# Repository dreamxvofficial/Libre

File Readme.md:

# Libre By DreamXV #
## It is an E-Ink Reading Device made for portability and mostly for warm-up week of *halflife.hackclub.com*. I have always been a fan of Kindle but its price is too high and it is not that customizable so I thought of making my own e-ink reader. ##
---
## Specs ##
- **Processor** ESP32-S3-WROOM-1-N16R8
- **Display** Waveshare 4.2", 400×300, B/W, SPI
- **Battery** 3.7 V Li-Po, 2000 mAh
- **MicroSD card**	16/32 GB 
- **USB-C** USB 2.0 Type-C receptacle
- **5 UI buttons** 6×6 × ~5 mm tactile push button
- **Power switch** SPDT slide switch

## Inspo Look ##

## Approximate BOM : ##

| Part            | Specification                   | Qty |
| --------------- | ------------------------------- | --: |
| E-Ink Display   | Waveshare 4.2" 400×300 B/W, SPI |   1 |
| Microcontroller | ESP32-S3-DevKitC-1-N16R8V       |   1 |
| Storage         | 16–32GB MicroSD Card + Socket   |   1 |
| Battery         | 3.7V 3000mAh Li-Po              |   1 |
| Charging        | MCP73831 Li-Po Charging Circuit |   1 |
| Power Switch    | SPDT ON/OFF Slide Switch        |   1 |
| Navigation      | 6×6mm SMD Tactile Buttons       |   5 |
| PCB             | Custom 2-Layer PCB              |   1 |
| Enclosure       | Custom 3D-Printed Case          |   1 |

## ** Approximate BOM ~ $110 or ~₹10,500 INR ** ##

## Schematic ##
### So i used AI for planing the connections of schematics and it just made me wanna die so yeah i dont know what to write more but i have connected the screen mcu micro sd and buttons together i dont know how but yes i have connected ###

## PCB ## 
### I just wanna give up mannnnnnnnnnn! >>>>>>>>>>3 I had to change the whole design as PCB was not as size of CAD so here is the new PCB with MCU ESP 32, 5 buttons 1 slider button and Micro SD Card ##

## CAD ##
### CAD design for Libre. It is 130 mm height and 78.5 mm width with a space for PCB, Buttons and E-Ink Display ##

## Final BOM ##

# DreamXV Libre — Final BOM

| Part | Qty | Unit Price (INR) | Total (INR) | Price Basis | Design Ref |
|---|---:|---:|---:|---|---|
| Waveshare 4.2-inch E-Ink Module B, 400x300 | 1 | ₹4,861.00 | ₹4,861.00 | Amazon India / current listing checked | Main display |
| ESP32-S3-DEVKITC-1-N16R8V | 1 | ₹1,500.00 | ₹1,500.00 | Indian/Amazon market listing checked | Main MCU board |
| Li-Po battery 3.7V 3000mAh | 1 | ₹500.00 | ₹500.00 | Indian hobby-retailer budget | Battery |
| Custom PCB | 1 | ₹1,000.00 | ₹1,000.00 | User budget | PCB fabrication |
| 3D-printed enclosure | 1 | ₹960.00 | ₹960.00 | User budget: $10 | 3D printing |
| Molex 104031-0811 MicroSD socket | 1 | ₹100.00 | ₹100.00 | Indian distributor budget | J2 |
| JST-PH 2-pin battery connector | 1 | ₹40.00 | ₹40.00 | Indian hobby-retailer budget | J3 |
| 8-pin display connector/header | 1 | ₹50.00 | ₹50.00 | Indian hobby-retailer budget | J1 |
| MCP73831-2-OT Li-Po charger IC | 1 | ₹80.00 | ₹80.00 | Indian distributor budget | U2 |
| AP2112K-3.3 LDO | 1 | ₹50.00 | ₹50.00 | Indian distributor budget | U3 |
| TL3305AF160QG SMD tactile button | 5 | ₹48.00 | ₹240.00 | Robu India listing | SW1-SW5 |
| C&K JS102011SAQN SPDT SMD switch | 1 | ₹150.00 | ₹150.00 | Indian distributor budget | SW6 |
| 1uF 0805 MLCC | 2 | ₹10.00 | ₹20.00 | Robu India example | C1-C2 |
| 4.7uF MLCC | 2 | ₹15.00 | ₹30.00 | Indian distributor budget | C3-C4 |
| 100nF 0805 MLCC | 1 | ₹3.00 | ₹3.00 | Indian distributor budget | C5 |
| 2kΩ 0805 resistor | 1 | ₹2.00 | ₹2.00 | Indian distributor budget | R1 |
| 200kΩ 0805 resistor | 2 | ₹0.31 | ₹0.62 | Robu India example | R2-R3 |

## Total Cost

- **Total INR:** ₹9,586.62
- **Exchange Rate:** ₹95.95 = $1
- **Total USD:** $99.91
- **Budget:** $100
- **Status:** UNDER $100

## Firmware ##

### ** The firmware is written for the ESP32-S3 and handles the main functions of Libre like the E-Ink display, MicroSD card, 5 navigation buttons and battery monitoring. It also has a simple file browser for selecting books and basic TXT reading. PDF files can be detected and listed, with proper PDF rendering planned for a future version. ** ###

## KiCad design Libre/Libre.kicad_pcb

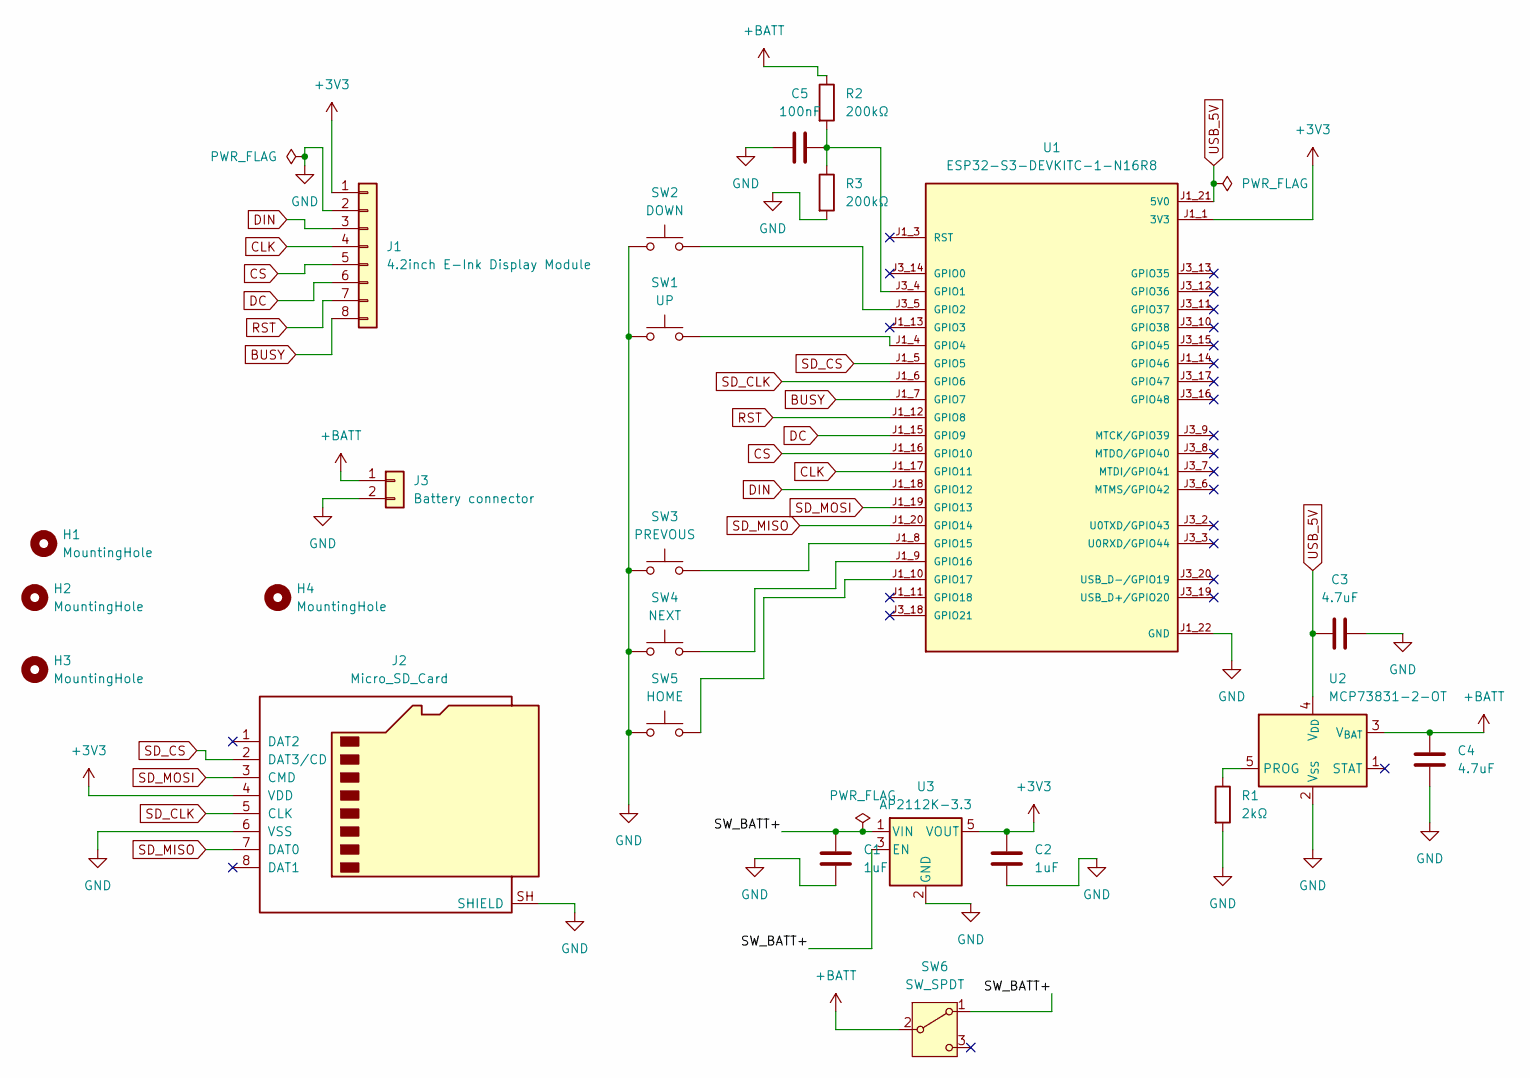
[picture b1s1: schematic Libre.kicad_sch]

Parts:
C1, C2: 1uF; C_0603_1608Metric
C3, C4: 4.7uF; C_0805_2012Metric
C5: 100nF; C_0603_1608Metric
H1, H2, H3, H4: MountingHole; MountingHole_2.5mm
J1: 4.2inch E-Ink Display Module; PinHeader_1x08_P2.54mm_Vertical
J2: Micro_SD_Card; microSD_HC_Molex_104031-0811
J3: Battery connector; JST_PH_S2B-PH-K_1x02_P2.00mm_Horizontal
R1: 2kΩ; R_0603_1608Metric
R2, R3: 200kΩ; R_0603_1608Metric
SW1: UP; SW_SPST_TL3305A
SW2: DOWN; SW_SPST_TL3305A
SW3: PREVOUS; SW_SPST_TL3305A
SW4: NEXT; SW_SPST_TL3305A
SW5: HOME; SW_SPST_TL3305A
SW6: SW_SPDT; SW_SPDT_CK_JS102011SAQN
U1: ESP32-S3-DEVKITC-1-N16R8; XCVR_ESP32-S3-DEVKITC-1-N16R8V; PARTREV V1
U2: MCP73831-2-OT; SOT-23-5
U3: AP2112K-3.3; SOT-23-5

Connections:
+3V3: C2.1, J1.1, J2.4 (VDD), U1.J1_1 (3V3), U1.J1_2 (3V3), U3.5 (VOUT)
+BATT: C4.1, J3.1, R2.1, SW6.2 (B), U2.3 (V_{BAT})
/SW_BATT+: C1.1, SW6.1 (A), U3.1 (VIN), U3.3 (EN)
BUSY: J1.8, U1.J1_7 (GPIO7)
CLK: J1.4, U1.J1_17 (GPIO11)
CS: J1.5, U1.J1_16 (GPIO10)
DC: J1.6, U1.J1_15 (GPIO9)
DIN: J1.3, U1.J1_18 (GPIO12)
GND: C1.2, C2.2, C3.2, C4.2, C5.1, J1.2, J2.6 (VSS), J2.SH (SHIELD), J3.2, R1.2, R3.2, SW1.1, SW2.1, SW3.1, SW4.1, SW5.1, U1.J1_22 (GND), U1.J3_1 (GND), U1.J3_21 (GND), U1.J3_22 (GND), U2.2 (V_{SS}), U3.2 (GND)
unnamed: C5.2, R2.2, R3.1, U1.J3_4 (GPIO1)
unnamed: SW2.2, U1.J3_5 (GPIO2)
unnamed: SW1.2, U1.J1_4 (GPIO4)
unnamed: SW3.2, U1.J1_8 (GPIO15)
unnamed: SW4.2, U1.J1_9 (GPIO16)
unnamed: SW5.2, U1.J1_10 (GPIO17)
unnamed: R1.1, U2.5 (PROG)
RST: J1.7, U1.J1_12 (GPIO8)
SD_CLK: J2.5 (CLK), U1.J1_6 (GPIO6)
SD_CS: J2.2 (DAT3/CD), U1.J1_5 (GPIO5)
SD_MISO: J2.7 (DAT0), U1.J1_20 (GPIO14)
SD_MOSI: J2.3 (CMD), U1.J1_19 (GPIO13)
USB_5V: C3.1, U1.J1_21 (5V0), U2.4 (V_{DD})

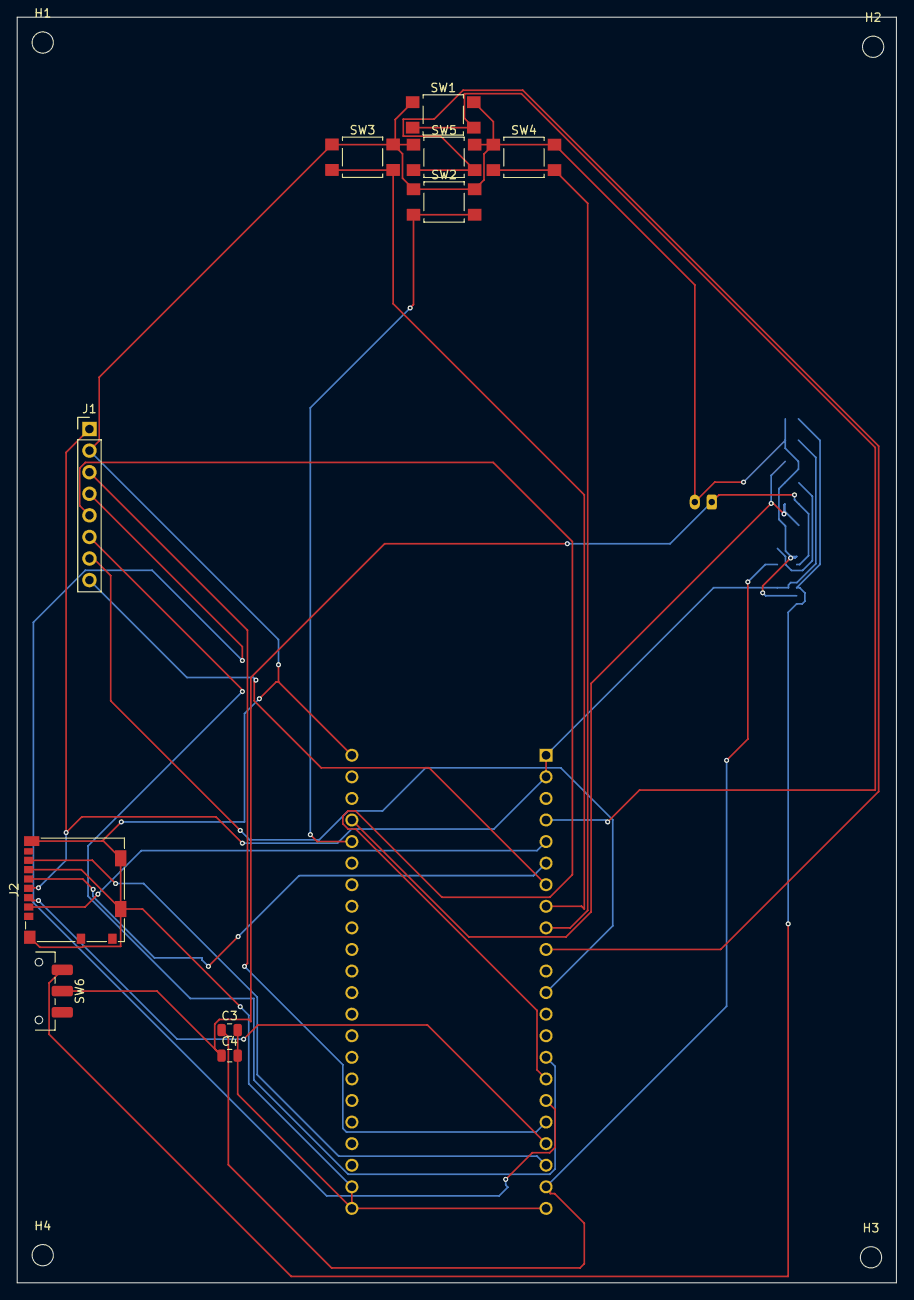
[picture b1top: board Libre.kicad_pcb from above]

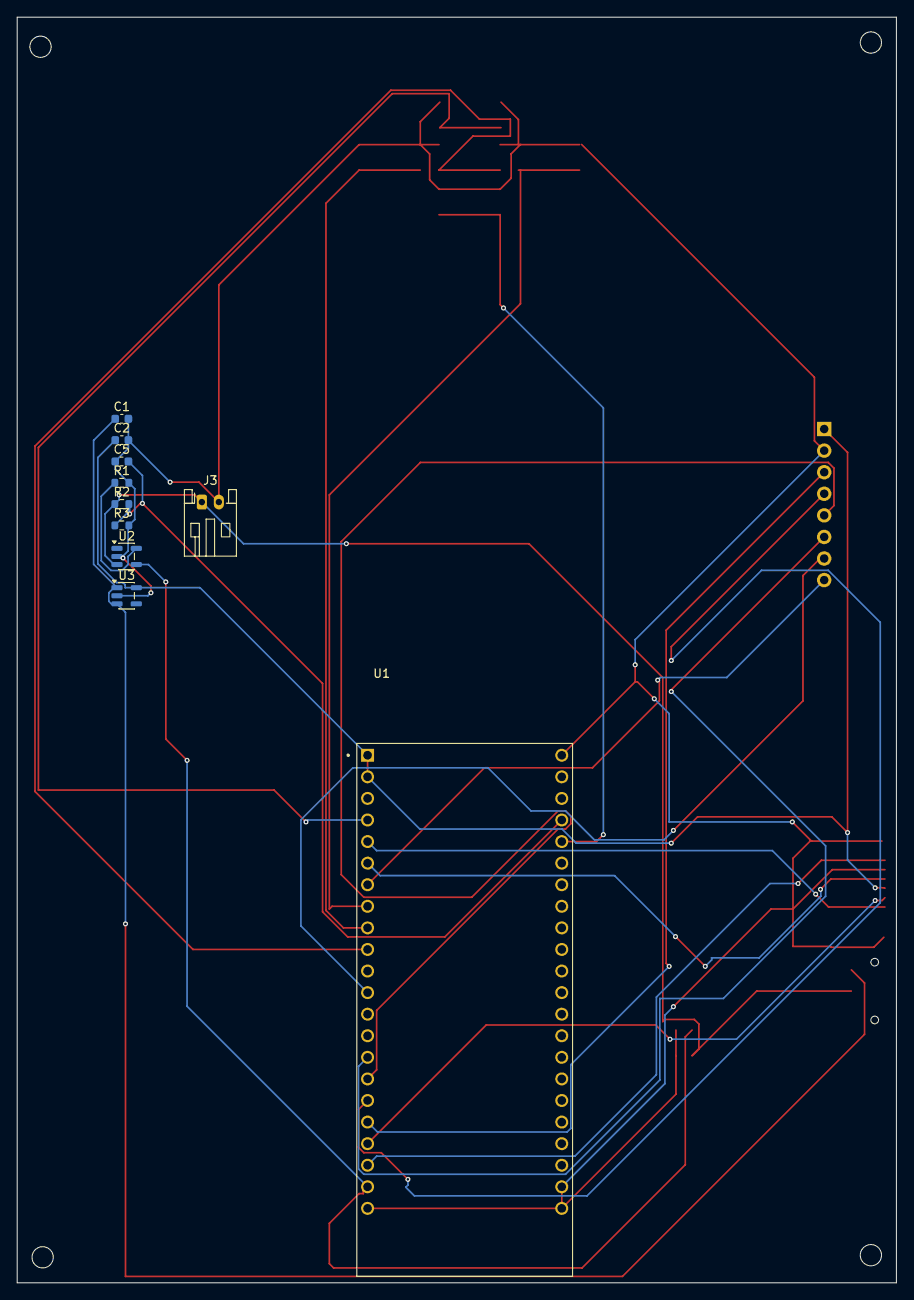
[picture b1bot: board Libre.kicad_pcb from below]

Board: 2 copper layers, 103.5 x 149.0 mm, 24 parts (10 on the bottom side), 22 nets.

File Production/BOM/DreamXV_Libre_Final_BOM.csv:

Part,Qty,Unit Price INR,Total INR,Price Basis,Design Ref
"Waveshare 4.2-inch E-Ink Module B, 400x300",1,4861.0,4861.0,Amazon India / current listing checked,Main display
ESP32-S3-DEVKITC-1-N16R8V,1,1500.0,1500.0,Indian/Amazon market listing checked,Main MCU board
Li-Po battery 3.7V 3000mAh,1,500.0,500.0,Indian hobby-retailer budget,Battery
Custom PCB,1,1000.0,1000.0,User budget,PCB fabrication
3D-printed enclosure,1,960.0,960.0,User budget: $10,3D printing
Molex 104031-0811 MicroSD socket,1,100.0,100.0,Indian distributor budget,J2
JST-PH 2-pin battery connector,1,40.0,40.0,Indian hobby-retailer budget,J3
8-pin display connector/header,1,50.0,50.0,Indian hobby-retailer budget,J1
MCP73831-2-OT Li-Po charger IC,1,80.0,80.0,Indian distributor budget,U2
AP2112K-3.3 LDO,1,50.0,50.0,Indian distributor budget,U3
TL3305AF160QG SMD tactile button,5,48.0,240.0,Robu India listing,SW1-SW5
C&K JS102011SAQN SPDT SMD switch,1,150.0,150.0,Indian distributor budget,SW6
1uF 0805 MLCC,2,10.0,20.0,Robu India example,C1-C2
4.7uF MLCC,2,15.0,30.0,Indian distributor budget,C3-C4
100nF 0805 MLCC,1,3.0,3.0,Indian distributor budget,C5
2kΩ 0805 resistor,1,2.0,2.0,Indian distributor budget,R1
200kΩ 0805 resistor,2,0.31,0.62,Robu India example,R2-R3
TOTAL,,,9586.62,₹95.95/USD,
TOTAL USD,,,,$99.91,
BUDGET STATUS,,,,UNDER $100,

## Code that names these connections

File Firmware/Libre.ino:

#include <Arduino.h>
#include <SPI.h>
#include <SD.h>
#include <GxEPD2_BW.h>
#include <Fonts/FreeMonoBold9pt7b.h>
#include <Fonts/FreeSansBold9pt7b.h>

#define BTN_NEXT 16
#define BTN_PREVIOUS 15
#define BTN_UP 4
#define BTN_DOWN 2
#define BTN_HOME 17

#define EPD_CS 10
#define EPD_DC 9
#define EPD_RST 8
#define EPD_BUSY 7

#define SD_CS 5
#define SD_SCK 12
#define SD_MISO 13
#define SD_MOSI 11

GxEPD2_BW<GxEPD2_420, GxEPD2_420::HEIGHT> display(
  GxEPD2_420(EPD_CS, EPD_DC, EPD_RST, EPD_BUSY)
);

SPIClass sdSPI(FSPI);

struct Button {
    unit8_t pin;
    bool lastState;
};

Button buttons[] = {
    {BTN_NEXT, true},
    {BTN_PREVIOUS, true},
    {BTN_UP, true},
    {BTN_DOWN, true},
    {BTN_HOME, true},
};

enum ButtonEvent {
    NONE,
    NEXT,
    PREVIOUS,
    UP,
    DOWN,
    HOME,
};

ButtonEvent readButton(){
    const uint8_t pins[] = {
        BTN_UP, BTN_DOWN, BTN_HOME, BTN_NEXT, BTN_PREVIOUS
    };

    for (int i=0; i<5; i++){
        bool state = digitalRead(pins[i]);
         if (state == LOW && buttons[i].lastState == HIGH) {
      delay(25);
      if (digitalRead(pins[i]) == LOW) {
        buttons[i].lastState = LOW;
        return (ButtonEvent)(i + 1);
      }
    }
    if (state == HIGH) {
      buttons[i].lastState = HIGH;
    }
  }
  return NONE;
}

const int MAX_BOOKS = 100;
String books[MAX_BOOKS];
int bookCount = 0;
int selectedBook = 0;

bool isBookFile(const String &name) {
    String lower = name;
    lower.toLowerCase()

    return lower.endsWith(".pdf") ||
           lower.endsWith(".epub") ||
           lower.endsWith(".txt");
           lower.endsWith(".text");
}

void scanBooks() {
    bookCount = 0;

    File root = SD.open("/" );
    if (!root){
        return;
    }
    File file = root.openNextFile();

    while(file && bookCount < MAX_BOOKS) {
        if(file.isDirectory()){
            String name = String(file.name());
            
            if (isBookFile(name)){
                books[bookCount++] = name;
            }
        }  
      file.close();
      file = root.openNextFile();
    }
    root.close();

  if (selectedBook >= bookCount) {
    selectedBook = max(0, bookCount - 1);
  }
}

float readButtonVoltage(){
    const float ADC_REFERENCE = 3.3f;
    const float DIVIDER_RATIO = 2.0f;

    unit16_t raw = analogRead(BATTERY_ADC);
    float vadc = (raw / 4095.0f) * ADC_REFERENCE;
    return vadc * DIVIDER_RATIO;
}

int batteryPercent(float voltage){

  if (voltage >= 4.20) return 100;
  if (voltage >= 4.10) return 90;
  if (voltage >= 4.00) return 75;
  if (voltage >= 3.90) return 60;
  if (voltage >= 3.80) return 45;
  if (voltage >= 3.70) return 30;
  if (voltage >= 3.60) return 15;
  if (voltage >= 3.50) return 5;
  return 0;
}

void drawHeader(const char *title){
  display.setFont(&FreeMonoBold9pt7b);
  display.setTextColor(GxEPD_BLACK);
  display.setCursor(8, 20);
  display.print(title);

  display.drawLine(5, 27, display.width() - 5, 27, GxEPD_BLACK);
}

void drawBattery(){
    float v = readBatteryVoltage();
    int p = batteryPercent(v);

    String text = String(p)+"%";
    display.setFont(&FreeMonoBold19pt7b);
    display.setTextColor(GxEPD_BLACK);
    display.setCursor(display.width() - 55, 20);
    display.print(text);
}

void showMessage(const String &line1, const String &line2 = ""){
    display.setFullWindow();
    display.firstPage();
    do {
        display.fillScreen(GxEPD_WHITE);

        display.setFont(&FreeSansBold12pt7b);
        display.setTextColor(GxEPD_BLACK);
        display.setCursor(10, 40);
        display.print(line1);

        if (line2.length()) {
            display.setCursor(10, 65);
            display.print(line2);
        }
    } while (display.nextPage());
}

void drawLibrary(){
    display.setFullWindow();
    display.firstPage();

    do{
        display.fillScreen(GxEPD_WHITE);

        drawHeader("DREAMXV LIBRE");
        drawBattery();

        if (bookCount == 0) {
            display.setFont(&FreeMonoBold9pt7b);
            display.setCursor(10, 65);
            display.print("No books found.");
            display.setCursor(10, 90);
            display.print("Copy PDF/TXT to MicroSD.");
        } else {
            display.setFont(&FreeMonoBold9pt7b);

            int start = max(0, selectedBook - 4);
            int end = min(bookCount, start + 8);

            for (int i = start; i < end; i++) {
                int y = 50 + ((i - start) * 28);

                if (i == selectedBook) {
                    display.fillRect(5, y - 17, display.width() - 10, 23, GxEPD_BLACK);
                    display.setTextColor(GxEPD_WHITE);
                } else {
                    display.setTextColor(GxEPD_BLACK);
                }

                String name = books[i];
                if (name.length() > 37) {
                    name = name.substring(0, 34) + "...";
                }
                
                display.setCursor(10, y);
                display.print(name);
            }
        }
    } while (display.nextPage());
}

void showTextPage(File &file, uint32_t startPosition) {
  const int linesPerPage = 16;
  const int charsPerLine = 48;

  file.seek(startPosition);

  String lines[linesPerPage];
  int lineCount = 0;

  while (file.available() && lineCount < linesPerPage) {
    String line = file.readStringUntil('\n');
    line.replace("\r", "");

    while (line.length() > 0 && lineCount < linesPerPage) {
      if (line.length() <= charsPerLine) {
        lines[lineCount++] = line;
        line = "";
      } else {
        lines[lineCount++] = line.substring(0, charsPerLine);
        line = line.substring(charsPerLine);
      }
    }
  }

  display.setFullWindow();
  display.firstPage();

  do {
    display.fillScreen(GxEPD_WHITE);
    display.setFont(&FreeMonoBold9pt7b);
    display.setTextColor(GxEPD_BLACK);

    for (int i = 0; i < lineCount; i++) {
      display.setCursor(5, 20 + (i * 18));
      display.print(lines[i]);
    }
  } while (display.nextPage());
}

void readTextBook(const String &path) {
  File file = SD.open(path, FILE_READ);

  if (!file) {
    showMessage("Cannot open file");
    delay(1000);
    return;
  }

  uint32_t position = 0;

  showTextPage(file, position);

  while (true) {
    ButtonEvent event = readButton();

    if (event == HOME || event == PREVIOUS) {
      break;
    }

    if (event == NEXT) {
      if (position + 1 < file.size()) {

        position += 700;
        if (position >= file.size()) {
          position = file.size() > 700 ? file.size() - 700 : 0;
        }
        showTextPage(file, position);
      }
    }

    if (event == UP) {
      if (position >= 700) {
        position -= 700;
        showTextPage(file, position);
      }
    }

    delay(10);
  }

  file.close();
}

void renderPdfPage(const String &path, int pageNumber) {

  showMessage("PDF selected:", path);
  delay(1500);
  showMessage("PDF renderer", "not installed");
  delay(1500);
}

void openBook() {
  if (bookCount == 0) return;

  String path = books[selectedBook];
  String lower = path;
  lower.toLowerCase();

  if (lower.endsWith(".txt") || lower.endsWith(".text")) {
    readTextBook(path);
  } else if (lower.endsWith(".pdf")) {
    renderPdfPage(path, 1);
  }
}

void setup() {
  Serial.begin(115200);
  delay(500);

  pinMode(BTN_UP, INPUT_PULLUP);
  pinMode(BTN_DOWN, INPUT_PULLUP);
  pinMode(BTN_PREVIOUS, INPUT_PULLUP);
  pinMode(BTN_NEXT, INPUT_PULLUP);
  pinMode(BTN_HOME, INPUT_PULLUP);

  pinMode(BATTERY_ADC, INPUT);
  analogReadResolution(12);

  display.init(115200);
  display.setRotation(1);

  showMessage("DREAMXV LIBRE", "Starting...");
  delay(800);

  sdSPI.begin(SD_SCK, SD_MISO, SD_MOSI, SD_CS);

  if (!SD.begin(SD_CS, sdSPI)) {
    showMessage("MicroSD error", "Check card/wiring");
    delay(1500);
  } else {
    scanBooks();
  }

  drawLibrary();
}

void loop() {
  ButtonEvent event = readButton();

  switch (event) {
    case UP:
      if (bookCount > 0) {
        selectedBook--;
        if (selectedBook < 0) {
          selectedBook = bookCount - 1;
        }
        drawLibrary();
      }
      break;

    case DOWN:
      if (bookCount > 0) {
        selectedBook++;
        if (selectedBook >= bookCount) {
          selectedBook = 0;
        }
        drawLibrary();
      }
      break;

    case NEXT:
      openBook();
      drawLibrary();
      break;

    case PREVIOUS:

      scanBooks();
      drawLibrary();
      break;

    case HOME:
      scanBooks();
      selectedBook = 0;
      drawLibrary();
      break;

    case NONE:
      break;
  }

  delay(10);
}
